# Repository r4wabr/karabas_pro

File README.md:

# Karabas-Pro

**Yet another FPGA ZX Spectrum clone ;)**

## Intro

ZX Spectrum compatible machine with a soft CPU, FDD and HDD (CF card) controllers, PS/2 keyboard/mouse, ESP8266 UART, RTC, VGA output and all logic inside the Altera FPGA **EP4CE6**.

## The idea

The idea was to make a smaller Profi (Профи) ZX Spectrum clone, with real FDD and HDD controllers. The board size fits the dimensions of the real 3.5" floppy drive. 

## Firmwares

**The main firmware is finished and currently it implements:**

1) ZX Spectrum classic and profi hi-res hi-color mode (with palette) (512x240)
2) ZX Profi CMR ports for extended peripherial
3) FDD controller that works both in CP/M and classic modes
4) HDD controller (works in Profi CP/M mode and PQ-DOS mode)
5) PS/2 keyboard (XT keyboard emulation)
6) PS/2 mouse (kempston mouse and serial MS mouse emulation)
7) VGA output (requires a monitor with 50Hz support)
8) Turbosound (2 x AY-3-8912), Soundrive and SAA1099 (SAA will work only on EP4CE10 due to lack of free LEs in EP4CE6)
9) Kempston joystick support
10) SEGA joystick support
11) RTC (profi), emulated read/write support
12) SD card access via Z-Controller emulation
13) Turbo 7 MHz (and Turbo 14 Mhz on EP4CE10)
14) ZX UNO simple UART @115200 for ESP8266 module (a secondary ZX UNO UART available on uBus connector for EP4CE10)
15) An additional ROM bank with **PQ-DOS BIOS**
16) An additional ROM bank with **Flash Tool** by **Doctor Max** to upgrade the FGPA firmware and ROM banks without programmer
17) An additional ROM bank with **FDImage Tool** by **Doctor Max** to extract TRD, SCL, PRO, TD0 and FDI images on real floppies
18) OSD menu
19) OSD full-screen overlay with easy-to-change options, RTC setup, etc.

## More info

**ERRATA for PCB rev.A:** [See ERRATA Rev.A](https://github.com/r4wabr/karabas_pro/blob/master/ERRATA-REVA.md).

**ERRATA for PCB rev.B:** [See ERRATA Rev.B](https://github.com/r4wabr/karabas_pro/blob/master/ERRATA-REVB.md).

**ERRATA for PCB rev.С:** [See ERRATA Rev.С](https://github.com/r4wabr/karabas_pro/blob/master/ERRATA-REVC.md).

**Latest stable revision:** rev.DS'.

**Latest development revision:** rev.E.

**PCB changelog:** [PCB changelog](https://github.com/r4wabr/karabas_pro/blob/master/CHANGELOG-PCB.md).

**Profi firmware** [Download a Profi firmware](https://github.com/r4wabr/karabas_pro/tree/master/firmware/releases/profi).

### Pre-production renders:

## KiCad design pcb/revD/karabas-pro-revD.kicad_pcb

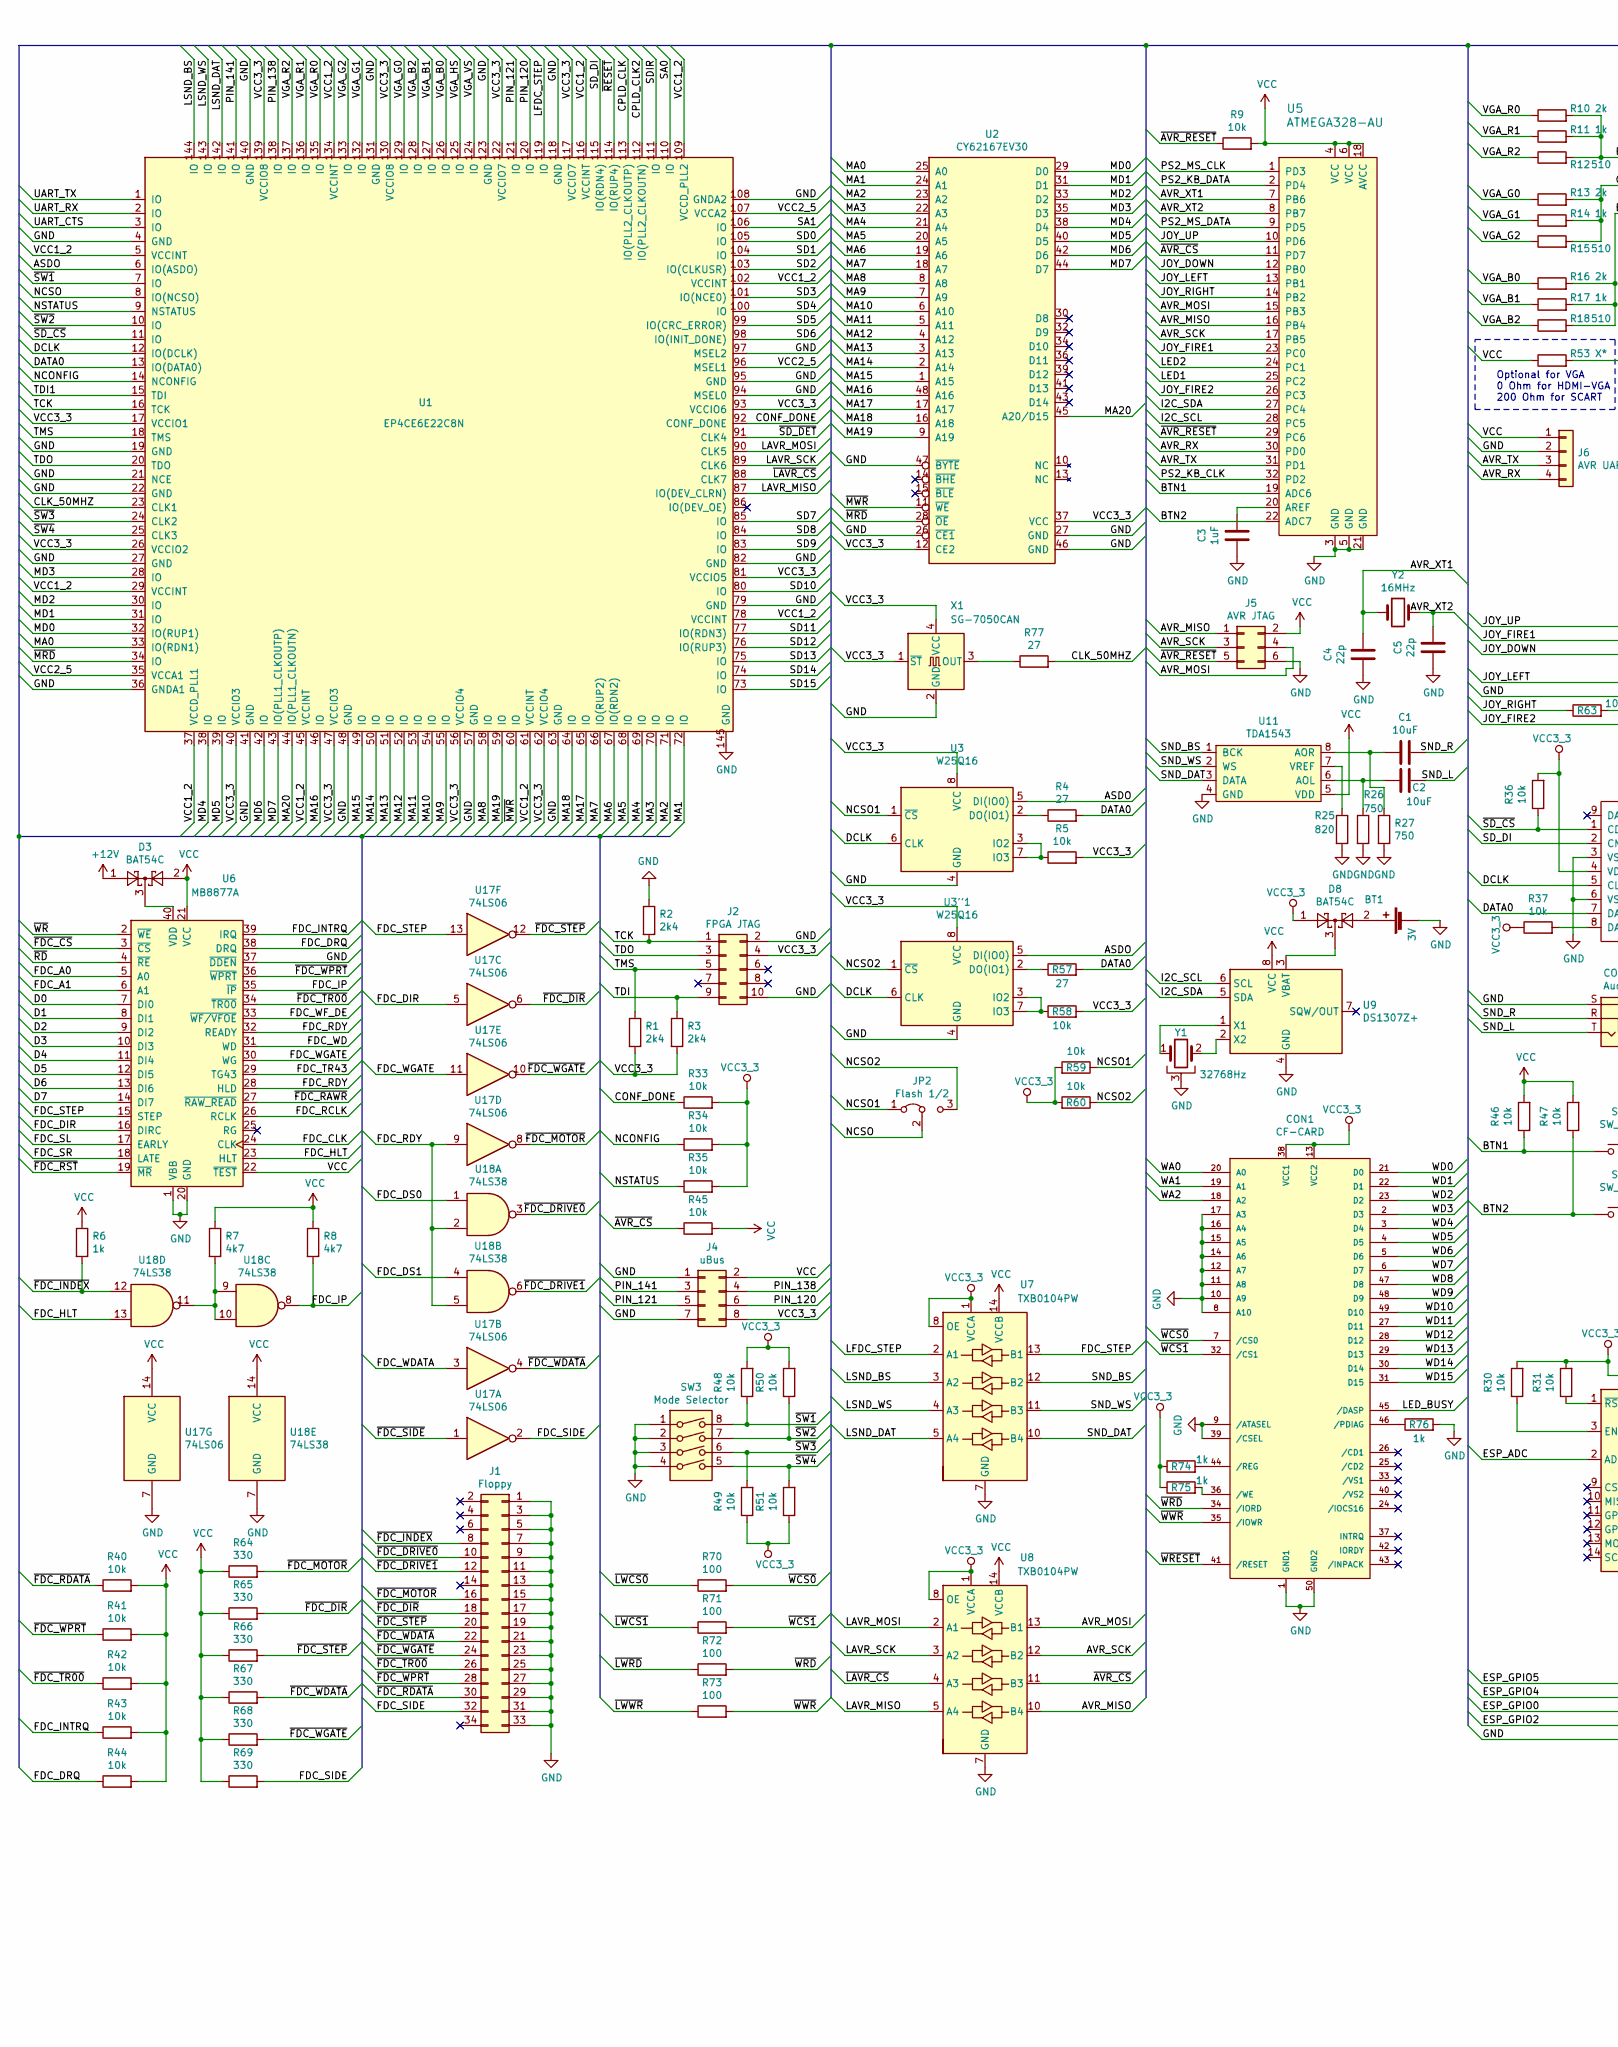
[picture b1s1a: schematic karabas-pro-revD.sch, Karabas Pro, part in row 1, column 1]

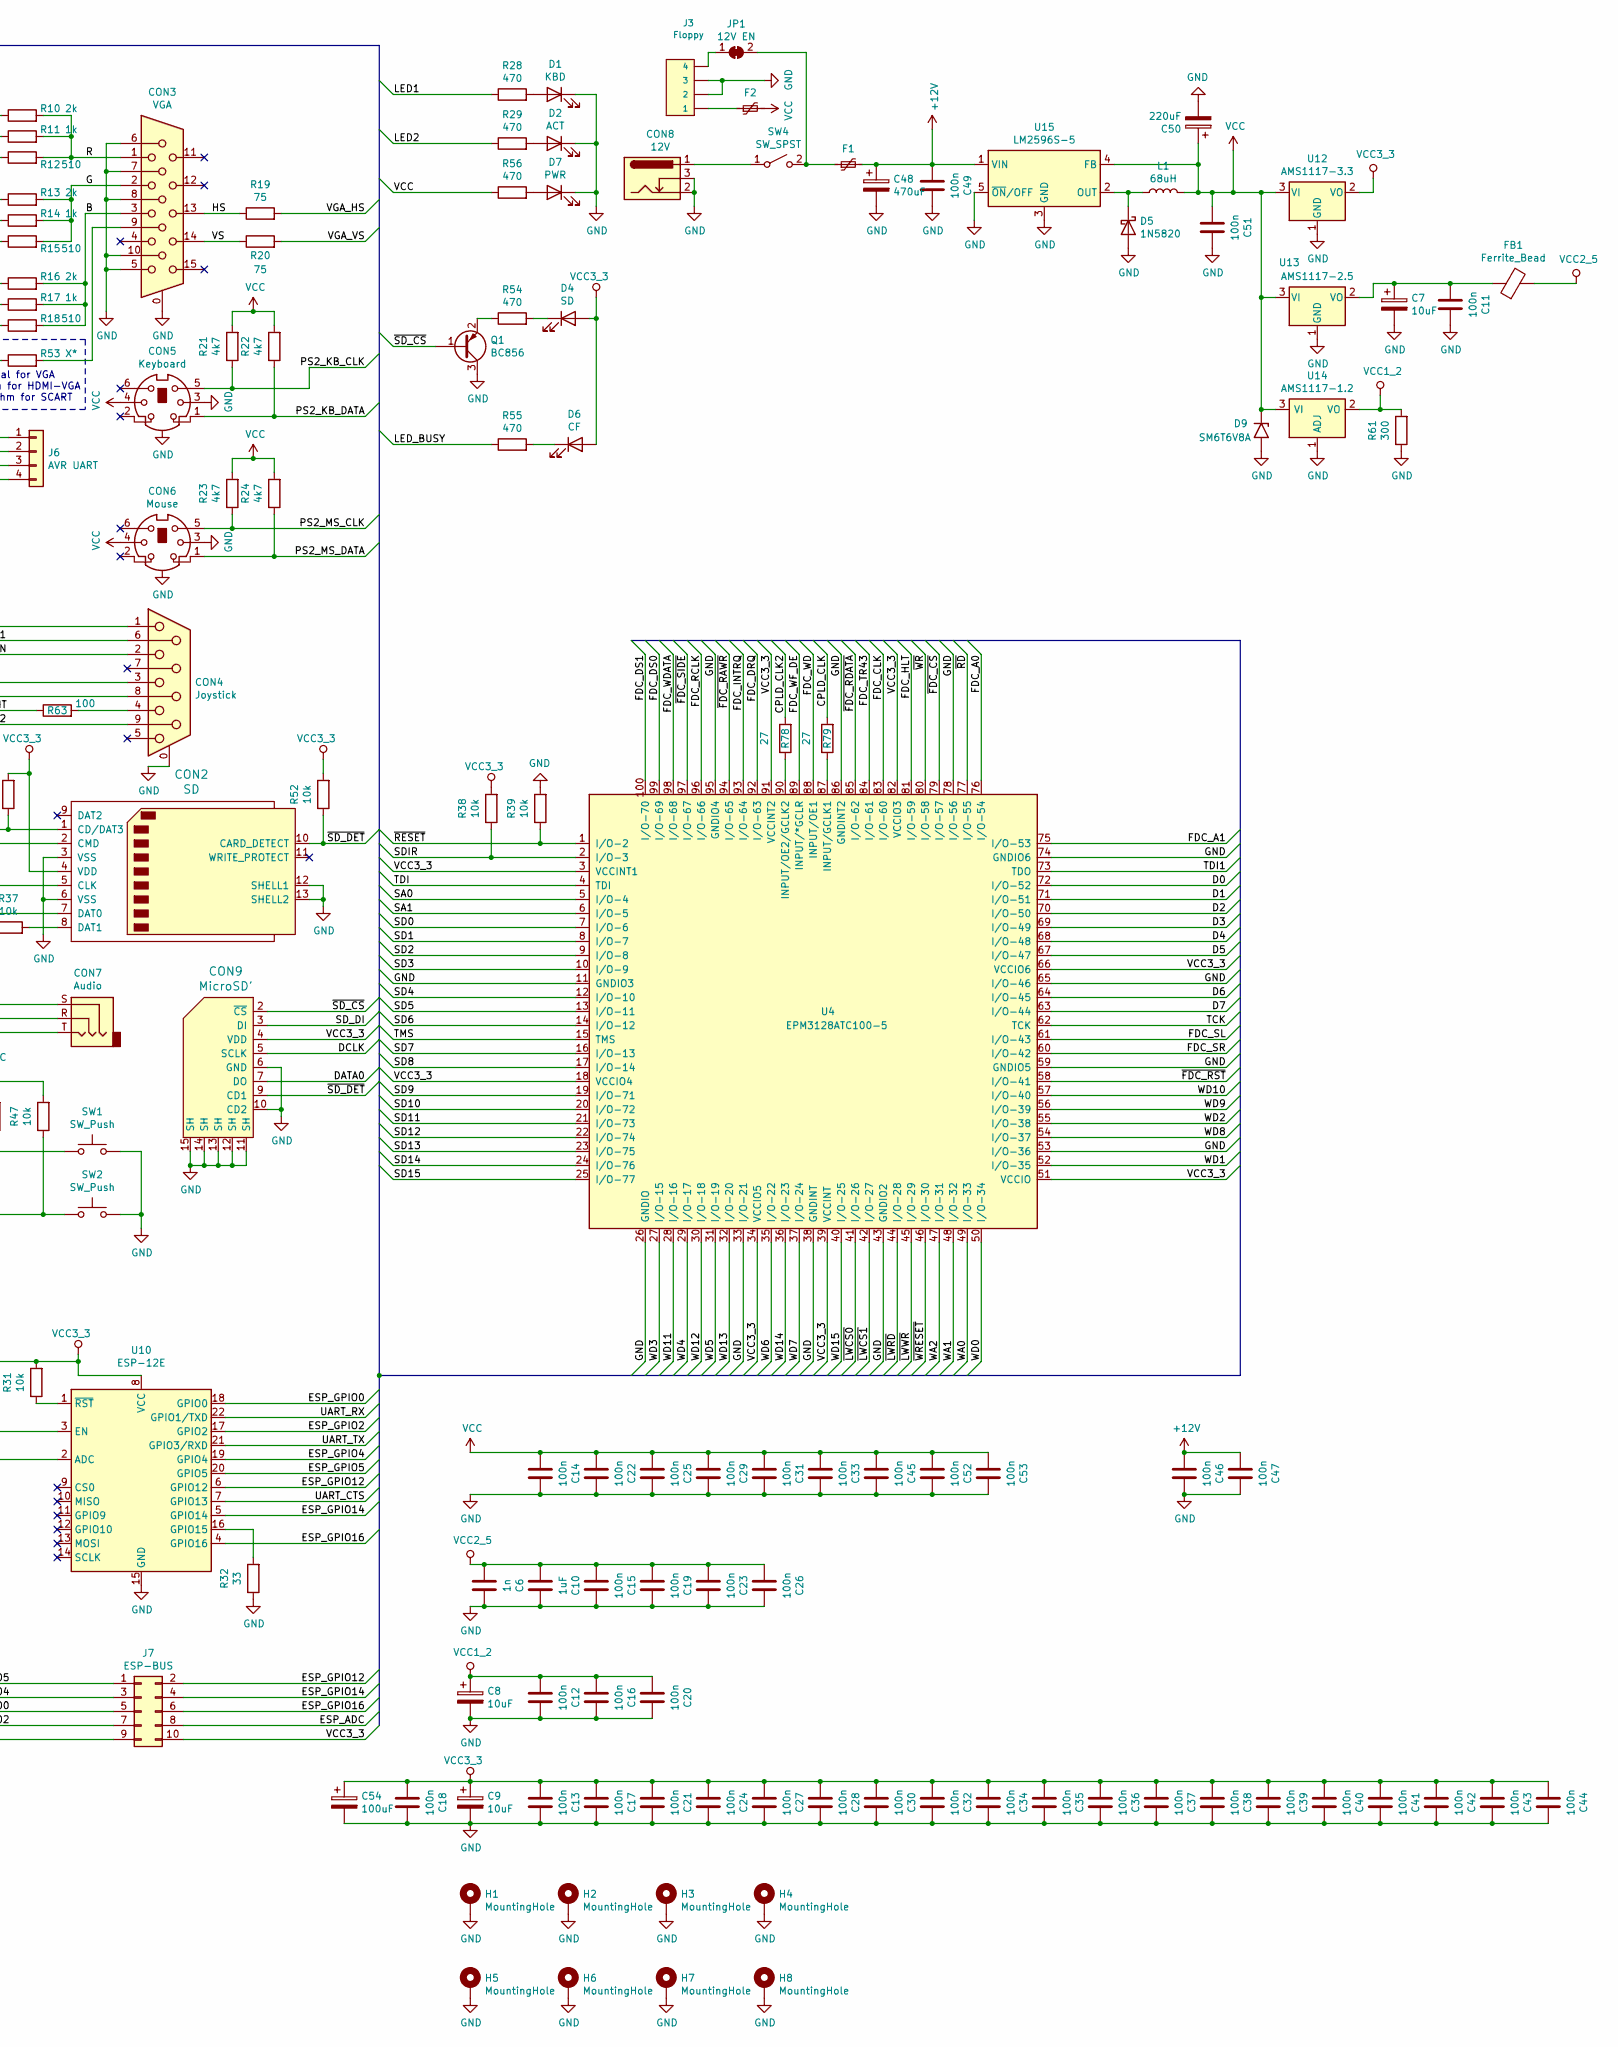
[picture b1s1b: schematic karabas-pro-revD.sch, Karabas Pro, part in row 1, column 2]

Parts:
BT1: 3V; BAT_BS-7-BLUE
C1, C2: 10uF; C_0805_2012Metric_Pad1.15x1.40mm_HandSolder
C3, C10: 1uF; C_0805_2012Metric_Pad1.15x1.40mm_HandSolder
C4, C5: 22p; C_0805_2012Metric_Pad1.15x1.40mm_HandSolder
C6: 1n; C_0805_2012Metric_Pad1.15x1.40mm_HandSolder
C7, C8, C9: 10uF; CP_EIA-7343-31_Kemet-D-uni
C11, C12, C13, C14, C15, C16, C17, C18, C19, C20, C21, C22, C23, C24, C25, C26, C27, C28, C29, C30, C31, C32, C33, C34, C35, C36, C37, C38, C39, C40, C41, C42, C43, C44, C45, C46, C47, C49, C51, C52, C53: 100n; C_0805_2012Metric_Pad1.15x1.40mm_HandSolder
C48: 470uF; CP_Radial_D8.0mm_P3.80mm
C50: 220uF; CP_Radial_D7.5mm_P2.50mm
C54: 100uF; CP_EIA-7343-31_Kemet-D-uni
CON1: CF-CARD; TE_1734451-1-LONG
CON2: SD; SD_TE_2041021-mod
CON3: VGA; DSUB-15-HD_Female_Horizontal_P2.29x1.98mm_EdgePinOffset3.03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
CON4: Joystick; DSUB-9_Male_Horizontal_P2.77x2.84mm_EdgePinOffset7.70mm_Hou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
CON5: Keyboard; MINI_DIN_6_33PRIMARY
CON6: Mouse; MINI_DIN_6_33PRIMARY
CON7: Audio; Jack_3.5mm_CUI_SJ1-3535NG_Horizontal
CON8: 12V; BarrelJack_Wuerth_6941xx301002
CON9: MicroSD'; MICRO_SD_MOLEX
D1: KBD; LED_0805_2012Metric_Pad1.15x1.40mm_HandSolder
D2: ACT; LED_0805_2012Metric_Pad1.15x1.40mm_HandSolder
D3, D8: BAT54C; SOT-23
D4: SD; LED_0805_2012Metric_Pad1.15x1.40mm_HandSolder
D5: 1N5820; D_DO-201AD_P15.24mm_Horizontal
D6: CF; LED_0805_2012Metric_Pad1.15x1.40mm_HandSolder
D7: PWR; LED_0805_2012Metric_Pad1.15x1.40mm_HandSolder
D9: SM6T6V8A; D_SMB
F1, F2: Polyfuse_Small; Fuse_1812_4532Metric_Castellated
FB1: Ferrite_Bead; L_0805_2012Metric_Pad1.15x1.40mm_HandSolder
H1, H2, H3, H4, H5, H6, H7, H8: MountingHole; MountingHole_3.5mm_Pad_Via
J1: Floppy; IDC-Header_2x17_P2.54mm_Vertical
J2: FPGA JTAG; IDC-Header_2x05_P2.54mm_Horizontal
J3: Floppy; PinHeader_1x04_P2.54mm_Vertical
J4: uBus; PinHeader_2x04_P2.54mm_Vertical
J5: AVR JTAG; IDC-Header_2x03_P2.54mm_Horizontal
J6: AVR UART; PinHeader_1x04_P2.54mm_Vertical
J7: ESP-BUS; PinHeader_2x05_P2.54mm_Vertical
JP1: 12V EN; SolderJumper-2_P1.3mm_Bridged_Pad1.0x1.5mm
JP2: Flash 1/2; PinHeader_1x03_P2.54mm_Vertical
L1: 68uH; L_12x12mm_H6mm
Q1: BC856; SOT-23
R1, R2, R3: 2k4; R_0805_2012Metric_Pad1.15x1.40mm_HandSolder
R4, R57, R77, R78, R79: 27; R_0805_2012Metric_Pad1.15x1.40mm_HandSolder
R5, R9, R30, R31, R33, R34, R35, R36, R37, R38, R39, R40, R41, R42, R43, R44, R45, R46, R47, R48, R49, R50, R51, R52, R58, R59, R60: 10k; R_0805_2012Metric_Pad1.15x1.40mm_HandSolder
R6, R11, R14, R17, R74, R75, R76: 1k; R_0805_2012Metric_Pad1.15x1.40mm_HandSolder
R7, R8, R21, R22, R23, R24: 4k7; R_0805_2012Metric_Pad1.15x1.40mm_HandSolder
R10, R13, R16: 2k; R_0805_2012Metric_Pad1.15x1.40mm_HandSolder
R12, R15, R18: 510; R_0805_2012Metric_Pad1.15x1.40mm_HandSolder
R19, R20: 75; R_0805_2012Metric_Pad1.15x1.40mm_HandSolder
R25: 820; R_0805_2012Metric_Pad1.15x1.40mm_HandSolder
R26, R27: 750; R_0805_2012Metric_Pad1.15x1.40mm_HandSolder
R28, R29, R54, R55, R56: 470; R_0805_2012Metric_Pad1.15x1.40mm_HandSolder
R32: 33; R_0805_2012Metric_Pad1.15x1.40mm_HandSolder
R53: X*; R_0805_2012Metric_Pad1.15x1.40mm_HandSolder
R61: 300; R_0805_2012Metric_Pad1.15x1.40mm_HandSolder
R63, R70, R71, R72, R73: 100; R_0805_2012Metric_Pad1.15x1.40mm_HandSolder
R64, R65, R66, R67, R68, R69: 330; R_0805_2012Metric_Pad1.15x1.40mm_HandSolder
SW1, SW2: SW_Push; SW_Tactile_SPST_Angled_PTS645Vx58-2LFS
SW3: Mode Selector; SW_DIP_SPSTx04_Piano_CTS_Series194-4MSTN_W7.62mm_P2.54mm
SW4: SW_SPST; SW_CuK_OS102011MA1QN1_SPDT_Angled
U1: EP4CE6E22C8N; ALTERA-QFP-145
U2: CY62167EV30; TSOP-I-48_18.4x12mm_P0.5mm
U3, U3''1: W25Q16; SOIC-8_5.23x5.23mm_P1.27mm
U4: EPM3128ATC100-5; LQFP-100_14x14mm_P0.5mm
U5: ATMEGA328-AU; TQFP-32_7x7mm_P0.8mm; MPN ATMEGA328-AU; Digi-Key_PN ATMEGA328-AU-ND
U6: MB8877A; DIP-40_W15.24mm
U7, U8: TXB0104PW; TSSOP-14_4.4x5mm_P0.65mm
U9: DS1307Z+; SOIC-8_3.9x4.9mm_P1.27mm
U10: ESP-12E
U11: TDA1543; DIP-8_W7.62mm
U12: AMS1117-3.3; TO-252-2
U13: AMS1117-2.5; SOT-223-3_TabPin2
U14: AMS1117-1.2; SOT-223-3_TabPin2
U15: LM2596S-5; TO-263-5_TabPin3
U17: 74LS06; DIP-14_W7.62mm
U18: 74LS38; DIP-14_W7.62mm
X1: SG-7050CAN; Oscillator_SMD_SeikoEpson_SG8002CA-4Pin_7.0x5.0mm
Y1: 32768Hz; Crystal_AT310_D3.0mm_L10.0mm_Horizontal_1EP_style2
Y2: 16MHz; Crystal_HC49-U_Vertical

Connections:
+12V: C46.1, C47.1, C48.1, C49.1, D3.1, F1.2, U15.1 (VIN)
/ASDO: U1.6 (IO(ASDO)), U3.5 (DI(IO0)), U3''1.5 (DI(IO0))
/AVR_MISO: J5.1, U5.16 (PB4), U8.10 (B4)
/AVR_MOSI: J5.4, U5.15 (PB3), U8.13 (B1)
/AVR_RX: J6.4, U5.30 (PD0)
/AVR_SCK: J5.3, U5.17 (PB5), U8.12 (B2)
/AVR_TX: J6.3, U5.31 (PD1)
/AVR_XT1: C4.2, U5.7 (PB6), Y2.1
/AVR_XT2: C5.2, U5.8 (PB7), Y2.2
/B: CON3.3, R16.2, R17.2, R18.2
/BTN1: R46.1, SW1.1, U5.19 (ADC6)
/BTN2: R47.1, SW2.1, U5.22 (ADC7)
/CLK_50MHZ: R77.2, U1.23 (CLK1)
/CONF_DONE: R33.1, U1.92 (CONF_DONE)
/CPLD_CLK: R79.2, U1.113 (IO(PLL2_CLKOUTP))
/CPLD_CLK2: R78.2, U1.112 (IO(PLL2_CLKOUTN))
/D0: U4.72 (I/O-52), U6.7 (DI0)
/D1: U4.71 (I/O-51), U6.8 (DI1)
/D2: U4.70 (I/O-50), U6.9 (DI2)
/D3: U4.69 (I/O-49), U6.10 (DI3)
/D4: U4.68 (I/O-48), U6.11 (DI4)
/D5: U4.67 (I/O-47), U6.12 (DI5)
/D6: U4.64 (I/O-45), U6.13 (DI6)
/D7: U4.63 (I/O-44), U6.14 (DI7)
/DATA0: CON2.7 (DAT0), CON9.7 (DO), R4.2, R57.2, U1.13 (IO(DATA0))
/DCLK: CON2.5 (CLK), CON9.5 (SCLK), U1.12 (IO(DCLK)), U3.6 (CLK), U3''1.6 (CLK)
/ESP_ADC: J7.8, U10.2 (ADC)
/ESP_GPIO0: J7.5, U10.18 (GPIO0)
/ESP_GPIO2: J7.7, U10.17 (GPIO2)
/ESP_GPIO4: J7.3, U10.19 (GPIO4)
/ESP_GPIO5: J7.1, U10.20 (GPIO5)
/ESP_GPIO12: J7.2, U10.6 (GPIO12)
/ESP_GPIO14: J7.4, U10.5 (GPIO14)
/ESP_GPIO16: J7.6, U10.4 (GPIO16)
/FDC_A0: U4.76 (I/O-54), U6.5 (A0)
/FDC_A1: U4.75 (I/O-53), U6.6 (A1)
/FDC_CLK: U4.83 (I/O-60), U6.24 (CLK)
/FDC_DIR: U6.16 (DIRC), U17.5
/FDC_DRQ: R44.1, U4.92 (I/O-63), U6.38 (DRQ)
/FDC_DS0: U4.99 (I/O-69), U18.1
/FDC_DS1: U4.100 (I/O-70), U18.4
/FDC_HLT: U4.81 (I/O-59), U6.23 (HLT), U18.13
/FDC_INTRQ: R43.1, U4.93 (I/O-64), U6.39 (IRQ)
/FDC_IP: R8.2, U6.35 (~IP), U18.8
/FDC_RCLK: U4.96 (I/O-66), U6.26 (RCLK)
/FDC_RDY: U6.28 (HLD), U6.32 (READY), U17.9, U18.2, U18.5
/FDC_SIDE: J1.32, R69.2, U17.2
/FDC_SL: U4.61 (I/O-43), U6.17 (EARLY)
/FDC_SR: U4.60 (I/O-42), U6.18 (LATE)
/FDC_STEP: U6.15 (STEP), U7.13 (B1), U17.13
/FDC_TR43: U4.84 (I/O-61), U6.29 (TG43)
/FDC_WD: U4.88 (INPUT/OE1), U6.31 (WD)
/FDC_WDATA: U4.98 (I/O-68), U17.3
/FDC_WF_DE: U4.89 (INPUT/*GCLR), U6.33 (~WF/VFOE~)
/FDC_WGATE: U6.30 (WG), U17.11
/G: CON3.2, R13.2, R14.2, R15.2
/HS: CON3.13, R19.1
/I2C_SCL: U5.28 (PC5), U9.6 (SCL)
/I2C_SDA: U5.27 (PC4), U9.5 (SDA)
/JOY_DOWN: CON4.2, U5.12 (PB0)
/JOY_FIRE1: CON4.6, U5.23 (PC0)
/JOY_FIRE2: CON4.9, U5.26 (PC3)
/JOY_LEFT: CON4.3, U5.13 (PB1)
/JOY_RIGHT: R63.1, U5.14 (PB2)
/JOY_UP: CON4.1, U5.10 (PD6)
/LAVR_MISO: U1.87 (IO(DEV_CLRN)), U8.5 (A4)
/LAVR_MOSI: U1.90 (CLK5), U8.2 (A1)
/LAVR_SCK: U1.89 (CLK6), U8.3 (A2)
/LED1: R28.1, U5.25 (PC2)
/LED2: R29.1, U5.24 (PC1)
/LED_BUSY: CON1.45 (/DASP), R55.1
/LFDC_STEP: U1.119 (IO), U7.2 (A1)
/LSND_BS: U1.144 (IO), U7.3 (A2)
/LSND_DAT: U1.142 (IO), U7.5 (A4)
/LSND_WS: U1.143 (IO), U7.4 (A3)
/MA0: U1.33 (IO(RDN1)), U2.25 (A0)
/MA1: U1.72 (IO), U2.24 (A1)
/MA2: U1.71 (IO), U2.23 (A2)
/MA3: U1.70 (IO), U2.22 (A3)
/MA4: U1.69 (IO), U2.21 (A4)
/MA5: U1.68 (IO), U2.20 (A5)
/MA6: U1.67 (IO(RDN2)), U2.19 (A6)
/MA7: U1.66 (IO(RUP2)), U2.18 (A7)
/MA8: U1.58 (IO), U2.8 (A8)
/MA9: U1.55 (IO), U2.7 (A9)
/MA10: U1.54 (IO), U2.6 (A10)
/MA11: U1.53 (IO), U2.5 (A11)
/MA12: U1.52 (IO), U2.4 (A12)
/MA13: U1.51 (IO), U2.3 (A13)
/MA14: U1.50 (IO), U2.2 (A14)
/MA15: U1.49 (IO), U2.1 (A15)
/MA16: U1.46 (IO), U2.48 (A16)
/MA17: U1.65 (IO), U2.17 (A17)
/MA18: U1.64 (IO), U2.16 (A18)
/MA19: U1.59 (IO), U2.9 (A19)
/MA20: U1.44 (IO(PLL1_CLKOUTN)), U2.45 (A20/D15)
/MD0: U1.32 (IO(RUP1)), U2.29 (D0)
/MD1: U1.31 (IO), U2.31 (D1)
/MD2: U1.30 (IO), U2.33 (D2)
/MD3: U1.28 (IO), U2.35 (D3)
/MD4: U1.38 (IO), U2.38 (D4)
/MD5: U1.39 (IO), U2.40 (D5)
/MD6: U1.42 (IO), U2.42 (D6)
/MD7: U1.43 (IO(PLL1_CLKOUTP)), U2.44 (D7)
/NCONFIG: R34.1, U1.14 (NCONFIG)
/NCSO: JP2.2 (C), U1.8 (IO(NCSO))
/NCSO1: JP2.1 (A), R59.1, U3.1 (~CS)
/NCSO2: JP2.3 (B), R60.1, U3''1.1 (~CS)
/NSTATUS: R35.1, U1.9 (NSTATUS)
/PIN_120: J4.6, U1.120 (IO)
/PIN_121: J4.5, U1.121 (IO)
/PIN_138: J4.4, U1.138 (IO)
/PIN_141: J4.3, U1.141 (IO)
/PS2_KB_CLK: CON5.5, R21.1, U5.32 (PD2)
/PS2_KB_DATA: CON5.1, R22.1, U5.2 (PD4)
/PS2_MS_CLK: CON6.5, R23.1, U5.1 (PD3)
/PS2_MS_DATA: CON6.1, R24.1, U5.9 (PD5)
/R: CON3.1, R10.2, R11.2, R12.2
/SA0: U1.110 (IO), U4.5 (I/O-4)
/SA1: U1.106 (IO), U4.6 (I/O-5)
/SD0: U1.105 (IO), U4.7 (I/O-6)
/SD1: U1.104 (IO), U4.8 (I/O-7)
/SD2: U1.103 (IO(CLKUSR)), U4.9 (I/O-8)
/SD3: U1.101 (IO(NCE0)), U4.10 (I/O-9)
/SD4: U1.100 (IO), U4.12 (I/O-10)
/SD5: U1.99 (IO(CRC_ERROR)), U4.13 (I/O-11)
/SD6: U1.98 (IO(INIT_DONE)), U4.14 (I/O-12)
/SD7: U1.85 (IO), U4.16 (I/O-13)
/SD8: U1.84 (IO), U4.17 (I/O-14)
/SD9: U1.83 (IO), U4.19 (I/O-71)
/SD10: U1.80 (IO), U4.20 (I/O-72)
/SD11: U1.77 (IO(RDN3)), U4.21 (I/O-73)
/SD12: U1.76 (IO(RUP3)), U4.22 (I/O-74)
/SD13: U1.75 (IO), U4.23 (I/O-75)
/SD14: U1.74 (IO), U4.24 (I/O-76)
/SD15: U1.73 (IO), U4.25 (I/O-77)
/SDIR: R38.1, U1.111 (IO), U4.2 (I/O-3)
/SD_DI: CON2.2 (CMD), CON9.3 (DI), U1.115 (IO(RDN4))
/SND_BS: U7.12 (B2), U11.1 (BCK)
/SND_DAT: U7.10 (B4), U11.3 (DATA)
/SND_L: C2.2, CON7.T
/SND_R: C1.2, CON7.R
/SND_WS: U7.11 (B3), U11.2 (WS)
/TCK: J2.1, R2.2, U1.16 (TCK), U4.62 (TCK)
/TDI: J2.9, R3.1, U4.4 (TDI)
/TDI1: U1.15 (TDI), U4.73 (TDO)
/TDO: J2.3, U1.20 (TDO)
/TMS: J2.5, R1.1, U1.18 (TMS), U4.15 (TMS)
/UART_CTS: U1.3 (IO), U10.7 (GPIO13)
/UART_RX: U1.2 (IO), U10.22 (GPIO1/TXD)
/UART_TX: U1.1 (IO), U10.21 (GPIO3/RXD)
/VGA_B0: R16.1, U1.126 (IO)
/VGA_B1: R17.1, U1.127 (IO)
/VGA_B2: R18.1, U1.128 (IO)
/VGA_G0: R13.1, U1.129 (IO)
/VGA_G1: R14.1, U1.132 (IO)
/VGA_G2: R15.1, U1.133 (IO)
/VGA_HS: R19.2, U1.125 (IO)
/VGA_R0: R10.1, U1.135 (IO)
/VGA_R1: R11.1, U1.136 (IO)
/VGA_R2: R12.1, U1.137 (IO)
/VGA_VS: R20.2, U1.124 (IO)
/VS: CON3.14, R20.1
/WA0: CON1.20 (A0), U4.49 (I/O-33)
/WA1: CON1.19 (A1), U4.48 (I/O-32)
/WA2: CON1.18 (A2), U4.47 (I/O-31)
/WD0: CON1.21 (D0), U4.50 (I/O-34)
/WD1: CON1.22 (D1), U4.52 (I/O-35)
/WD2: CON1.23 (D2), U4.55 (I/O-38)
/WD3: CON1.2 (D3), U4.27 (I/O-15)
/WD4: CON1.3 (D4), U4.29 (I/O-17)
/WD5: CON1.4 (D5), U4.31 (I/O-19)
/WD6: CON1.5 (D6), U4.35 (I/O-22)
/WD7: CON1.6 (D7), U4.37 (I/O-24)
/WD8: CON1.47 (D8), U4.54 (I/O-37)
/WD9: CON1.48 (D9), U4.56 (I/O-39)
/WD10: CON1.49 (D10), U4.57 (I/O-40)
/WD11: CON1.27 (D11), U4.28 (I/O-16)
/WD12: CON1.28 (D12), U4.30 (I/O-18)
/WD13: CON1.29 (D13), U4.32 (I/O-20)
/WD14: CON1.30 (D14), U4.36 (I/O-23)
/WD15: CON1.31 (D15), U4.40 (I/O-25)
/~AVR_CS: R45.1, U5.11 (PD7), U8.11 (B3)
/~AVR_RESET: J5.5, R9.1, U5.29 (PC6)
/~FDC_CS: U4.79 (I/O-57), U6.3 (~CS)
/~FDC_DIR: J1.18, R65.2, U17.6
/~FDC_DRIVE0: J1.10, U18.3
/~FDC_DRIVE1: J1.12, U18.6
/~FDC_INDEX: J1.8, R6.2, U18.12
/~FDC_MOTOR: J1.16, R64.2, U17.8
/~FDC_RAWR: U4.94 (I/O-65), U6.27 (~RAW_READ)
/~FDC_RDATA: J1.30, R40.1, U4.85 (I/O-62)
/~FDC_RST: U4.58 (I/O-41), U6.19 (~MR)
/~FDC_SIDE: U4.97 (I/O-67), U17.1
/~FDC_STEP: J1.20, R66.2, U17.12
/~FDC_TR00: J1.26, R42.1, U6.34 (~TR00)
/~FDC_WDATA: J1.22, R67.2, U17.4
/~FDC_WGATE: J1.24, R68.2, U17.10
/~FDC_WPRT: J1.28, R41.1, U6.36 (~WPRT)
/~LAVR_CS: U1.88 (CLK7), U8.4 (A3)
/~LWCS0: R70.1, U4.41 (I/O-26)
/~LWCS1: R71.1, U4.42 (I/O-27)
/~LWRD: R72.1, U4.44 (I/O-28)
/~LWWR: R73.1, U4.45 (I/O-29)
/~MRD: U1.34 (IO), U2.28 (~OE)
/~MWR: U1.60 (IO), U2.11 (~WE)
/~RD: U4.77 (I/O-55), U6.4 (~RE)
/~RESET: R39.1, U1.114 (IO(RUP4)), U4.1 (I/O-2)
/~SD_CS: CON2.1 (CD/DAT3), CON9.2 (~CS), Q1.1 (B), R36.1, U1.11 (IO)
/~SD_DET: CON2.10 (CARD_DETECT), CON9.9 (CD1), R52.1, U1.91 (CLK4)
/~SW1: R48.1, SW3.8, U1.7 (IO)
/~SW2: R50.1, SW3.7, U1.10 (IO)
/~SW3: R49.2, SW3.6, U1.24 (CLK2)
/~SW4: R51.2, SW3.5, U1.25 (CLK3)
/~WCS0: CON1.7 (/CS0), R70.2
/~WCS1: CON1.32 (/CS1), R71.2
/~WR: U4.80 (I/O-58), U6.2 (~WE)
/~WRD: CON1.34 (/IORD), R72.2
/~WRESET: CON1.41 (/RESET), U4.46 (I/O-30)
/~WWR: CON1.35 (/IOWR), R73.2
GND: BT1.2 (-), C3.1, C4.1, C5.1, C6.2, C7.2, C8.2, C9.2, C10.2, C11.2, C12.2, C13.2, C14.2, C15.2, C16.2, C17.2, C18.2, C19.2, C20.2, C21.2, C22.2, C23.2, C24.2, C25.2, C26.2, C27.2, C28.2, C29.2, C30.2, C31.2, C32.2, C33.2, C34.2, C35.2, C36.2, C37.2, C38.2, C39.2, C40.2, C41.2, C42.2, C43.2, C44.2, C45.2, C46.2, C47.2, C48.2, C49.2, C50.2, C51.2, C52.2, C53.2, C54.2, CON1.1 (GND1), CON1.8 (A10), CON1.9 (/ATASEL), CON1.10 (A9), CON1.11 (A8), CON1.12 (A7), CON1.14 (A6), CON1.15 (A5), CON1.16 (A4), CON1.17 (A3), CON1.39 (/CSEL), CON1.50 (GND2), CON2.3 (VSS), CON2.6 (VSS), CON2.12 (SHELL1), CON2.13 (SHELL2), CON3.0, CON3.5, CON3.6, CON3.7, CON3.8, CON3.10, CON4.0 (PAD), CON4.8, CON5.3, CON5.GND, CON6.3, CON6.GND, CON7.S, CON8.2, CON8.3, CON9.6 (GND), CON9.10 (CD2), CON9.11 (SH), CON9.12 (SH), CON9.13 (SH), CON9.14 (SH), CON9.15 (SH), D1.1 (K), D2.1 (K), D5.2 (A), D7.1 (K), D9.2 (A2), H1.1, H2.1, H3.1, H4.1, H5.1, H6.1, H7.1, H8.1, J1.1, J1.3, J1.5, J1.7, J1.9, J1.11, J1.13, J1.15, J1.17, J1.19, J1.21, J1.23, J1.25, J1.27, J1.29, J1.31, J1.33, J2.2, J2.10, J3.2, J3.3, J4.1, J4.7, J5.6, J6.2, J7.9, Q1.3 (C), R2.1, R25.2, R26.2, R27.2, R32.1, R39.2, R61.1, R76.2, SW1.2, SW2.2, SW3.1, SW3.2, SW3.3, SW3.4, U1.4 (GND), U1.19 (GND), U1.21 (NCE), U1.22 (GND), U1.27 (GND), U1.36 (GNDA1), U1.41 (GND), U1.48 (GND), U1.57 (GND), U1.63 (GND), U1.79 (GND), U1.82 (GND), U1.94 (MSEL0), U1.95 (GND), U1.97 (MSEL2), U1.108 (GNDA2), U1.118 (GND), U1.123 (GND), U1.131 (GND), U1.140 (GND), U1.145 (GND), U2.26 (~CE1), U2.27 (GND), U2.46 (GND), U2.47 (~BYTE), U3.4 (GND), U3''1.4 (GND), U4.11 (GNDIO3), U4.26 (GNDIO), U4.33 (I/O-21), U4.38 (GNDINT), U4.43 (GNDIO2), U4.53 (I/O-36), U4.59 (GNDIO5), U4.65 (I/O-46), U4.74 (GNDIO6), U4.78 (I/O-56), U4.86 (GNDINT2), U4.95 (GNDIO4), U5.3 (GND), U5.5 (GND), U5.21 (GND), U6.1 (VBB), U6.20 (GND), U6.37 (~DDEN), U7.7 (GND), U8.7 (GND), U9.4 (GND), U10.15 (GND), U11.4 (GND), U12.1 (GND), U13.1 (GND), U14.1 (ADJ), U15.3 (GND), U15.5 (~ON~/OFF), U17.7 (GND), U18.7 (GND), X1.2 (GND), Y1.3
unnamed: BT1.1 (+), D8.2
unnamed: C1.1, R27.1, U11.8 (AOR)
unnamed: C2.1, R26.1, U11.6 (AOL)
unnamed: C3.2, U5.20 (AREF)
unnamed: C7.1, C11.1, FB1.1, U13.2 (VO)
unnamed: CON1.36 (/WE), R75.2
unnamed: CON1.44 (/REG), R74.2
unnamed: CON1.46 (/PDIAG), R76.1
unnamed: CON2.8 (DAT1), R37.2
unnamed: CON3.9, R53.2
unnamed: CON4.4, R63.2
unnamed: CON8.1, SW4.1 (A)
unnamed: D1.2 (A), R28.2
unnamed: D2.2 (A), R29.2
unnamed: D3.3, U6.40 (VDD)
unnamed: D4.1 (K), R54.2
unnamed: D5.1 (K), L1.1, U15.2 (OUT)
unnamed: D6.1 (K), R55.2
unnamed: D7.2 (A), R56.2
unnamed: D8.3, U9.3 (VBAT)
unnamed: F1.1, JP1.2 (B), SW4.2 (B)
unnamed: F2.1, J3.1
unnamed: J3.4, JP1.1 (A)
unnamed: Q1.2 (E), R54.1
unnamed: R4.1, U3.2 (DO(IO1))
unnamed: R5.1, U3.3 (IO2), U3.7 (IO3)
unnamed: R7.2, U18.9, U18.10, U18.11
unnamed: R25.1, U11.7 (VREF)
unnamed: R30.1, U10.3 (EN)
unnamed: R31.1, U10.1 (~RST)
unnamed: R32.2, U10.16 (GPIO15)
unnamed: R57.1, U3''1.2 (DO(IO1))
unnamed: R58.1, U3''1.3 (IO2), U3''1.7 (IO3)
unnamed: R77.1, X1.3 (OUT)
unnamed: R78.1, U4.90 (INPUT/OE2/GCLK2)
unnamed: R79.1, U4.87 (INPUT/GCLK1)
unnamed: U9.1 (X1), Y1.1
unnamed: U9.2 (X2), Y1.2
VCC: C14.1, C22.1, C25.1, C29.1, C31.1, C33.1, C45.1, C50.1, C51.1, C52.1, C53.1, CON5.4, CON6.4, D3.2, D9.1 (A1), F2.2, J4.2, J5.2, J6.1, L1.2, R6.1, R7.1, R8.1, R9.2, R21.2, R22.2, R23.2, R24.2, R40.2, R41.2, R42.2, R43.2, R44.2, R45.2, R46.2, R47.2, R53.1, R56.1, R64.1, R65.1, R66.1, R67.1, R68.1, R69.1, U5.4 (VCC), U5.6 (VCC), U5.18 (AVCC), U6.21 (VCC), U6.22 (~TEST), U7.14 (VCCB), U8.14 (VCCB), U9.8 (VCC), U11.5 (VDD), U12.3 (VI), U13.3 (VI), U14.3 (VI), U15.4 (FB), U17.14 (VCC), U18.14 (VCC)
VCC1_2: C8.1, C12.1, C16.1, C20.1, R61.2, U1.5 (VCCINT), U1.29 (VCCINT), U1.37 (VCCD_PLL1), U1.45 (VCCINT), U1.61 (VCCINT), U1.78 (VCCINT), U1.102 (VCCINT), U1.109 (VCCD_PLL2), U1.116 (VCCINT), U1.134 (VCCINT), U14.2 (VO)
VCC2_5: C6.1, C10.1, C15.1, C19.1, C23.1, C26.1, FB1.2, U1.35 (VCCA1), U1.96 (MSEL1), U1.107 (VCCA2)
VCC3_3: C9.1, C13.1, C17.1, C18.1, C21.1, C24.1, C27.1, C28.1, C30.1, C32.1, C34.1, C35.1, C36.1, C37.1, C38.1, C39.1, C40.1, C41.1, C42.1, C43.1, C44.1, C54.1, CON1.13 (VCC2), CON1.38 (VCC1), CON2.4 (VDD), CON9.4 (VDD), D4.2 (A), D6.2 (A), D8.1, J2.4, J4.8, J7.10, R1.2, R3.2, R5.2, R30.2, R31.2, R33.2, R34.2, R35.2, R36.2, R37.1, R38.2, R48.2, R49.1, R50.2, R51.1, R52.2, R58.2, R59.2, R60.2, R74.1, R75.1, U1.17 (VCCIO1), U1.26 (VCCIO2), U1.40 (VCCIO3), U1.47 (VCCIO3), U1.56 (VCCIO4), U1.62 (VCCIO4), U1.81 (VCCIO5), U1.93 (VCCIO6), U1.117 (VCCIO7), U1.122 (VCCIO7), U1.130 (VCCIO8), U1.139 (VCCIO8), U2.12 (CE2), U2.37 (VCC), U3.8 (VCC), U3''1.8 (VCC), U4.3 (VCCINT1), U4.18 (VCCIO4), U4.34 (VCCIO5), U4.39 (VCCINT), U4.51 (VCCIO), U4.66 (VCCIO6), U4.82 (VCCIO3), U4.91 (VCCINT2), U7.1 (VCCA), U7.8 (OE), U8.1 (VCCA), U8.8 (OE), U10.8 (VCC), U12.2 (VO), X1.1 (~ST), X1.4 (VCC)

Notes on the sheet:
Optional for VGA 0 Ohm for HDMI-VGA 200 Ohm for SCART

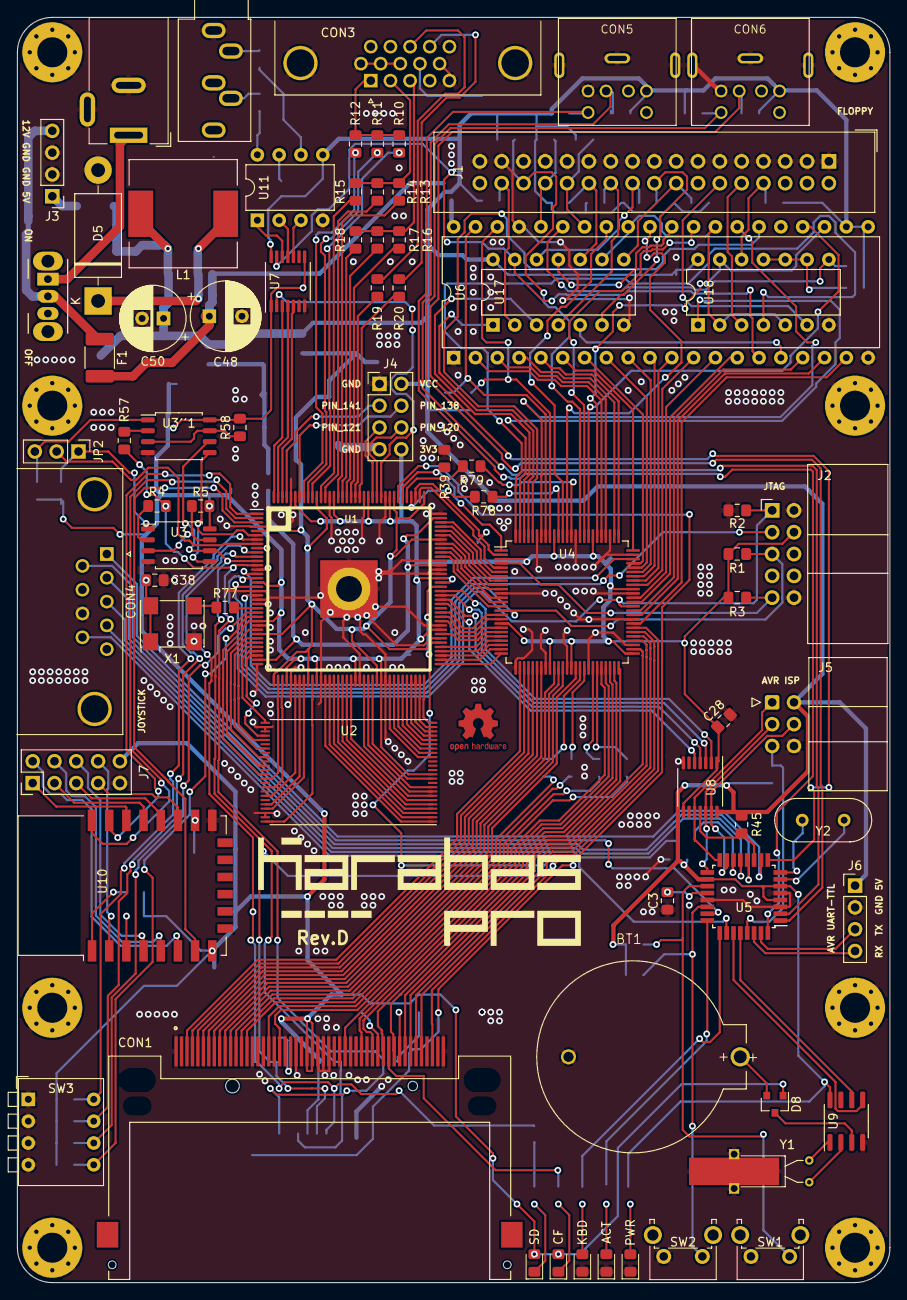
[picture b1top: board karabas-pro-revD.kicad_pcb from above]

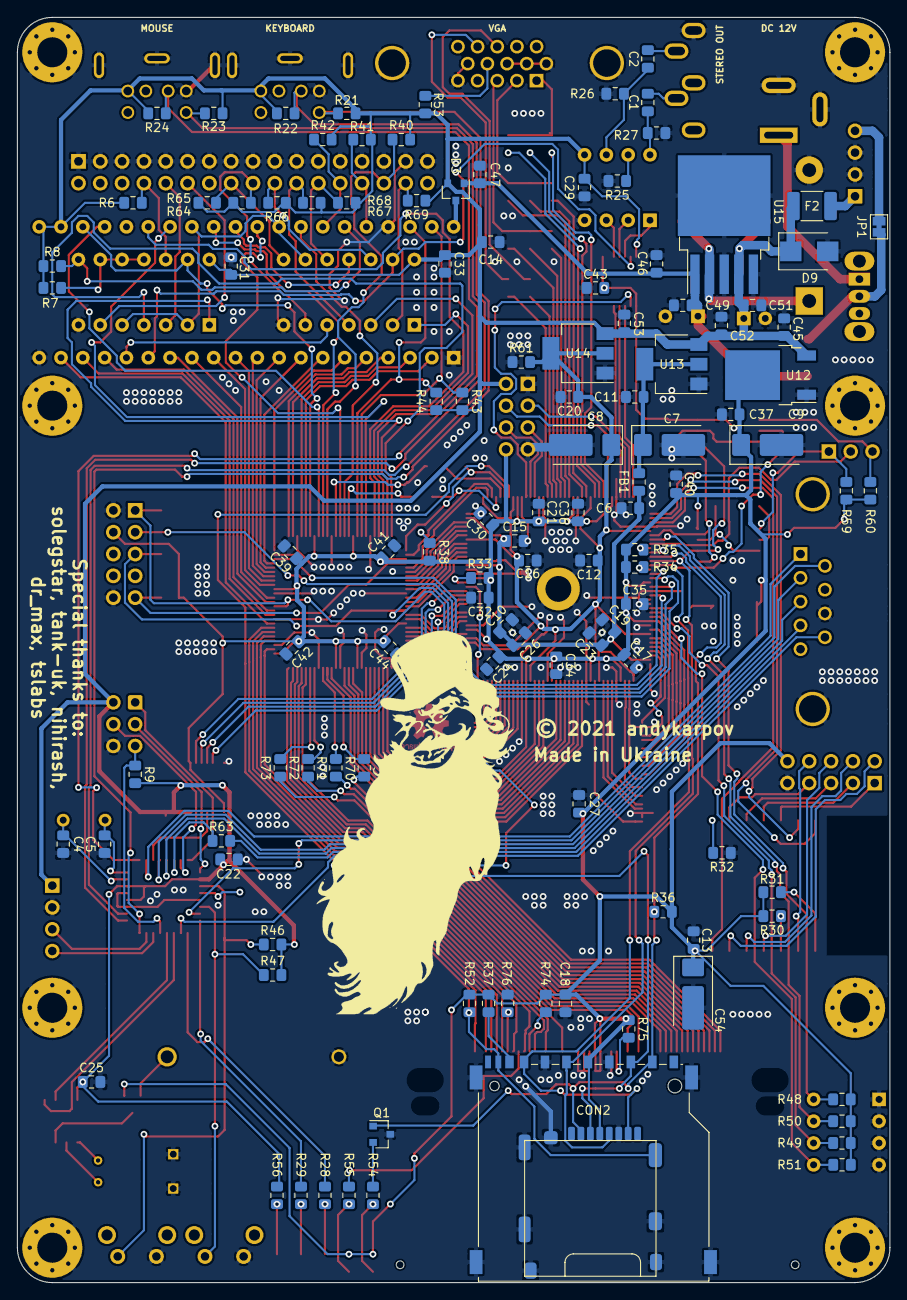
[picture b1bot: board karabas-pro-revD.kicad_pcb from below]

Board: 2 copper layers, 101.6 x 147.3 mm, 198 parts (116 on the bottom side), 263 nets.

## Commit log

2022-02-27 iam
    add files

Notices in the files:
pcb/revD/karabas-pro-revD.kicad_pcb:
© 2021 andykarpov
